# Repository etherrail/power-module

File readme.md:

# EtherRail Power Module
This module switches, reverses and measures a power district on a model railway.

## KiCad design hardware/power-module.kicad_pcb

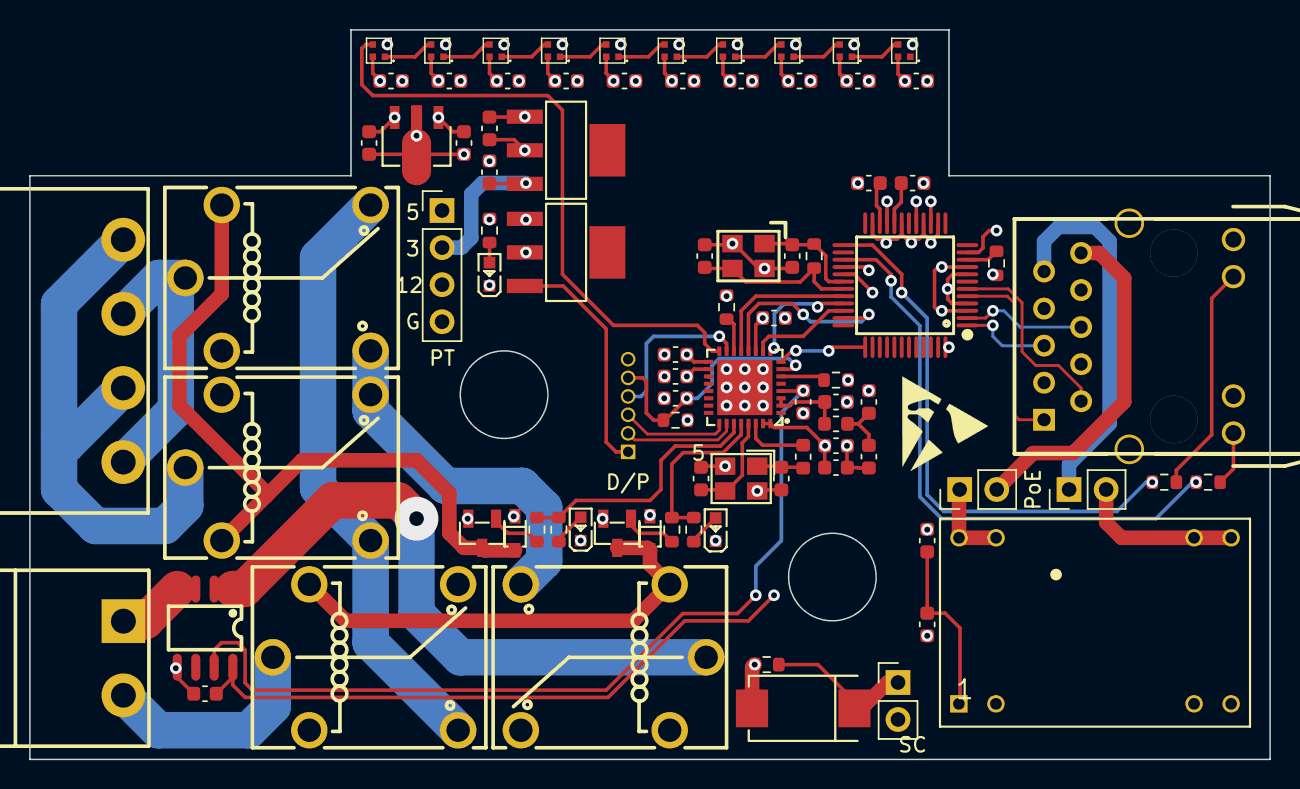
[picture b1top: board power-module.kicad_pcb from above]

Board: 4 copper layers, 85.0 x 50.0 mm, 87 parts (0 on the bottom side), 66 nets.

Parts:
C1, C2, C20: 0.1nF; C_0603_1608Metric
C3: 100uF 25V; C_0603_1608Metric
C4: 10uF 25V; C_0603_1608Metric
C5, C6: 4.7uF; C_0603_1608Metric
C7, C8: 18pF; C_0603_1608Metric
C9, C21, C25, C33: 1uF; C_0603_1608Metric
C10, C11, C12, C13, C14, C15, C19, C23, C24, C26, C28, C29, C30, C31, C34: 0.1uF; C_0603_1608Metric
C16, C17: 14pF; C_0603_1608Metric
C18: 0.33uF; C_0603_1608Metric
C22: 10nF; C_0603_1608Metric
C27: 10uF; C_0603_1608Metric
C32: TAJE337M016RNJ; CAP-SMD_L7.3-W4.3-R-RD
CN1: WJ2EDGRC-5.08-2P; CONN-TH_2P-P5.08_WJ2EDGRC-5.08-2P
D1, D2: BAS321,115; SOD-323_L1.8-W1.3-LS2.5-RD
H1: DZ127R-11-06-25; HDR-TH_6P-P1.27-V-M-A
J1: Conn_01x04_Pin; PinHeader_1x04_P2.54mm_Vertical
J2, J3, J4: Conn_01x02; PinHeader_1x02_P2.54mm_Vertical
K1, K2, K3, K4: SRA-12VDC-CL; RELAY-TH_SRA-X-CX
L1: 2.0nH; L_0603_1608Metric
L2: 24nH; L_0603_1608Metric
LED1, LED2, LED3: XL-1608UYC-06; LED0603-RD-YELLOW
P1: WJ2EDGRC-5.08-4P; CONN-TH_4P-P5.08_WJ2EDGRC-5.08-4P
Q1, Q2: SS8050_C2150; SOT-23-3_L2.9-W1.3-P1.90-LS2.4-BR
R1, R11: 560; R_0603_1608Metric
R2, R4: 56; R_0603_1608Metric
R3, R7, R10: 120; R_0603_1608Metric
R5: 12.4K 1%; R_0603_1608Metric
R6: 1M; R_0603_1608Metric
R8, R9, R12: 10K; R_0603_1608Metric
R13: 6.2k; R_0603_1608Metric
RJ1: HY931147C; RJ45-TH_HY931147C
U1, U5: AMS1117-3.3_C347222; SOT-223-4_L6.5-W3.5-P2.30-LS7.0-BR
U2: CC6903SO-10A; SOP-8_L4.9-W3.9-P1.27-LS6.0-BL
U3: W5500; LQFP-48_L7.0-W7.0-P0.50-LS9.0-BL
U4: ESP32-C3FH4; QFN-32_L5.0-W5.0-P0.50-TL-EP3.7
U6, U8, U9, U10, U11, U12, U15, U16, U17, U18: XL-1010RGBC-WS2812B; LED-SMD_4P-L1.0-W1.0-TL_XL-1010RGBC-WS2812B
U7: DP9900LP-12V; PWRM-TH_DP9900LP-5V
U13: L327S400H11L; CRYSTAL-SMD_4P-L3.2-W2.5-BL
U14: UMW78L05; SOT-89-3_L4.5-W2.5-P1.50-LS4.2-BR
X1: X322525MRB4SI; OSC-SMD_4P-L3.2-W2.5-BL_SIT8008BI

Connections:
+3.3V: C1.1, C20.1, C21.2, C22.2, C23.2, C24.1, C33.1, J1.3, R3.1, R8.2, R9.2, U1.2 (VOUT(TAB)), U2.8 (VCC), U3.4 (AVDD), U3.8 (AVDD), U3.11 (AVDD), U3.15 (AVDD), U3.17 (AVDD), U3.21 (AVDD), U3.28 (VDD), U4.11 (VDD3P3_RTC), U4.17 (VDD3P3_CPU), U4.18 (VDD_SPI), U4.31 (VDDA), U4.32 (VDDA), U5.2 (VOUT(TAB))
+5V: C10.1, C11.1, C12.1, C13.1, C14.1, C15.1, C19.1, C28.1, C29.1, C30.1, C31.1, J1.1, U6.2 (VDD), U8.2 (VDD), U9.2 (VDD), U10.2 (VDD), U11.2 (VDD), U12.2 (VDD), U14.1 (OUT), U15.2 (VDD), U16.2 (VDD), U17.2 (VDD), U18.2 (VDD)
+12V: C2.1, C3.2, C4.2, C18.1, D1.1 (K), D2.1 (K), J1.2, J4.2, K1.4, K2.3, K3.4, K4.3, U1.3 (VIN), U7.1 (+VDC), U7.2 (+VDC), U14.3 (IN)
/BOOT: H1.4, U4.15 (GPIO9)
/CURRENT SENSING INPUT: C34.2, U2.7 (OUT), U4.4 (XTAL_32K_P)
/ETHERNET RX +: RJ1.2, U3.6 (RXP)
/ETHERNET RX -: RJ1.1, U3.5 (RXN)
/ETHERNET TX +: RJ1.6, U3.2 (TXP)
/ETHERNET TX -: RJ1.5, U3.1 (TXN)
/LED ACTIVITY: R2.2, U3.27 (ACTLED)
/LED DATA IN: U4.16 (GPIO10), U6.4 (DIN)
/LED LINK: R4.2, U3.25 (LINKLED)
/POE IN +: J3.2, U7.5 (VIN+), U7.6 (VIN+)
/POE IN -: J2.1, U7.7 (VIN-), U7.8 (VIN-)
/RESET: C9.2, H1.5, R9.1, U4.7 (CHIP_EN)
/TRACK DIRECTION: R10.2, R11.2, U4.27 (U0RXD)
/TRACK OUT A: K3.5, P1.2, P1.4
/TRACK OUT B: K4.5, P1.1, P1.3
/TRACK POWER A: CN1.2, K1.5
/TRACK POWER B: K2.5, U2.1 (IP+), U2.2 (IP+)
/TRACK POWER ENABLE: R1.2, R7.2, U4.28 (U0TXD)
/TRACK POWER ENABLED A: K1.1, K3.2, K4.1
/TRACK POWER ENABLED B: K2.1, K3.1, K4.2
/USB +: H1.2, U4.26 (GPIO19)
/USB -: H1.3, U4.25 (GPIO18)
/WIZ RESET: U3.37 (RSTn), U4.8 (GPIO3)
/WIZ SPI CS: U3.32 (SCSn), U4.13 (MTDO)
/WIZ SPI MISO: U3.34 (MISO), U4.10 (MTDI)
/WIZ SPI MOSI: U3.35 (MOSI), U4.12 (MTCK)
/WIZ SPI SCLK: U3.33 (SCLK), U4.9 (MTMS)
GND: C1.2, C2.2, C3.1, C4.1, C5.2, C6.2, C7.2, C8.2, C9.1, C10.2, C11.2, C12.2, C13.2, C14.2, C15.2, C16.1, C17.1, C18.2, C19.2, C20.2, C21.1, C22.1, C23.1, C24.2, C25.1, C26.1, C27.1, C28.2, C29.2, C30.2, C31.2, C32.2, C33.2, C34.1, H1.6, J1.4, LED1.1 (K), LED2.1 (K), LED3.1 (K), Q1.2 (E), Q2.2 (E), R5.2, R12.1, R13.2, RJ1.12, RJ1.14, RJ1.GND1 (GND), RJ1.GND2 (GND), U1.1 (ADJ(GND)), U2.5 (GND), U3.3 (AGND), U3.9 (AGND), U3.14 (AGND), U3.16 (AGND), U3.19 (AGND), U3.23 (RSVD), U3.29 (GND), U3.48 (AGND), U4.33 (EP), U5.1 (ADJ(GND)), U6.3 (GND), U7.3 (-VDC), U8.3 (GND), U9.3 (GND), U10.3 (GND), U11.3 (GND), U12.3 (GND), U13.2 (GND), U13.4 (GND), U14.2 (GND), U15.3 (GND), U16.3 (GND), U17.3 (GND), U18.3 (GND), X1.2 (GND), X1.4 (GND)
unnamed: C16.2, L2.2, U13.1
unnamed: C25.2, L1.1, U4.2 (VDD3P3), U4.3 (VDD3P3)
unnamed: C26.2, C27.2, L1.2
unnamed: CN1.1, U2.3 (IP-), U2.4 (IP-)
unnamed: D1.2 (A), K1.3, K2.4, Q2.3 (C)
unnamed: D2.2 (A), K3.3, K4.4, Q1.3 (C)
unnamed: J2.2, RJ1.10
unnamed: J3.1, RJ1.9
unnamed: C32.1, J4.1, R13.1
unnamed: LED1.2 (A), R3.2
unnamed: LED2.2 (A), R7.1
unnamed: LED3.2 (A), R10.1
unnamed: Q1.1 (B), R11.1
unnamed: Q2.1 (B), R1.1
unnamed: R2.1, RJ1.11
unnamed: R4.1, RJ1.13
unnamed: C6.1, U3.22 (1V2O)
unnamed: R5.1, U3.10 (EXRES1)
unnamed: C5.1, U3.20 (TOCAP)
unnamed: C7.1, R6.2, U3.30 (XI/CLKIN), X1.1 (OSC1)
unnamed: C8.1, R6.1, U3.31 (XO), X1.3 (OSC2)
unnamed: R8.1, U4.6 (GPIO2)
unnamed: R12.2, U4.14 (GPIO8)
unnamed: C17.2, U4.29 (XTAL_N), U13.3
unnamed: L2.1, U4.30 (XTAL_P)
unnamed: H1.1, U5.3 (VIN)
unnamed: U6.1 (DOUT), U8.4 (DIN)
unnamed: U8.1 (DOUT), U9.4 (DIN)
unnamed: U9.1 (DOUT), U10.4 (DIN)
unnamed: U10.1 (DOUT), U11.4 (DIN)
unnamed: U11.1 (DOUT), U12.4 (DIN)
unnamed: U12.1 (DOUT), U15.4 (DIN)
unnamed: U15.1 (DOUT), U16.4 (DIN)
unnamed: U16.1 (DOUT), U17.4 (DIN)
unnamed: U17.1 (DOUT), U18.4 (DIN)

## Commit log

2024-05-30 Initial commit (v1b)
2024-05-30 Add basic readme
2024-06-02 Fix relay power supply, shrinked module to 1.5 DIN module widths
2024-06-07 Fix current sensing input on esp blocking WiFi communications
2024-06-07 Add case slotting and holes
2024-06-07 Fix relay switching transistors current rating
2025-01-02 Add wifi version
2025-01-02 Add PoE board
2025-01-04 Add routes and part placement
2025-01-06 Fix SPI pins, power supply current
2025-01-07 Fix crystal
2025-01-07 Add current sensing input capactior
